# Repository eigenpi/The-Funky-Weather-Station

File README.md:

# The-Funky-Weather-Station

## Description

This is a weather-station device built with an ESP32-C3 board and a Waveshare 2.9" e-paper display. It retrieves weather info from OpenWeatherMap. Time and date is also retrieved and displayed. Device needs access to a WiFi router. This repository contains all the design files for anyone to be able to replicate it.

## Video description

https://youtu.be/MDfy2SWch-s

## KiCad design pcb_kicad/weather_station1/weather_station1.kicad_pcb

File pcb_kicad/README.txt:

This is the entire project in KiCAD 9.0.6

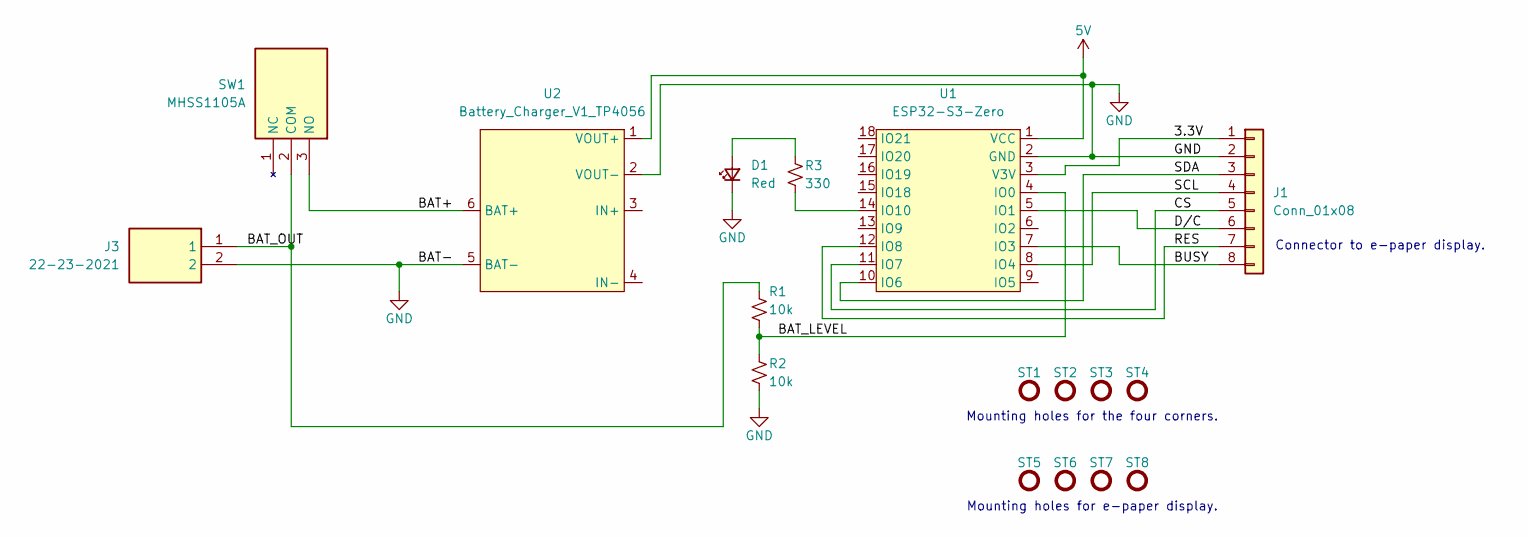
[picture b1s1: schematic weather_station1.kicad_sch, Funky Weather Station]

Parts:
D1: Red; LED_5mm_PTH_Red_NoSilk
J1: Conn_01x08; 1x08_P2.54mm
J3: 22-23-2021; SHDR2W87P0X254_1X2_493X635X1105P; Mouser Part Number 538-22-23-2021
R1, R2: 10k; R_Axial_DIN0207_L6.3mm_D2.5mm_P7.62mm_Horizontal
R3: 330; R_Axial_DIN0207_L6.3mm_D2.5mm_P7.62mm_Horizontal
ST1, ST2, ST3, ST4, ST5, ST6, ST7, ST8: Standoff; Standoff_Hole-2.75mm_Clearance-1.625mm
SW1: MHSS1105A; Mouser Part Number 642-MHSS1105A
U1: ESP32-S3-Zero; Waveshare-ESP32-C3-Zero
U2: Battery_Charger_V1_TP4056

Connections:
5V: U1.1 (VCC), U2.1 (VOUT+)
/3.3V: J1.1, U1.3 (V3V)
/BAT+: SW1.3 (NO), U2.6 (BAT+)
/BAT_LEVEL: R1.1, R2.2, U1.4 (IO0)
/BAT_OUT: J3.1, R1.2, SW1.2 (COM)
/BUSY: J1.8, U1.7 (IO3)
/CS: J1.5, U1.11 (IO7)
/D/C: J1.6, U1.5 (IO1)
/RES: J1.7, U1.12 (IO8)
/SCL: J1.4, U1.8 (IO4)
/SDA: J1.3, U1.10 (IO6)
GND: D1.1 (K), J1.2, J3.2, R2.1, U1.2 (GND), U2.2 (VOUT-), U2.5 (BAT-)
unnamed: D1.2 (A), R3.2
unnamed: R3.1, U1.14 (IO10)

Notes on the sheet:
Mounting holes for e-paper display.
Connector to e-paper display.
Mounting holes for the four corners.

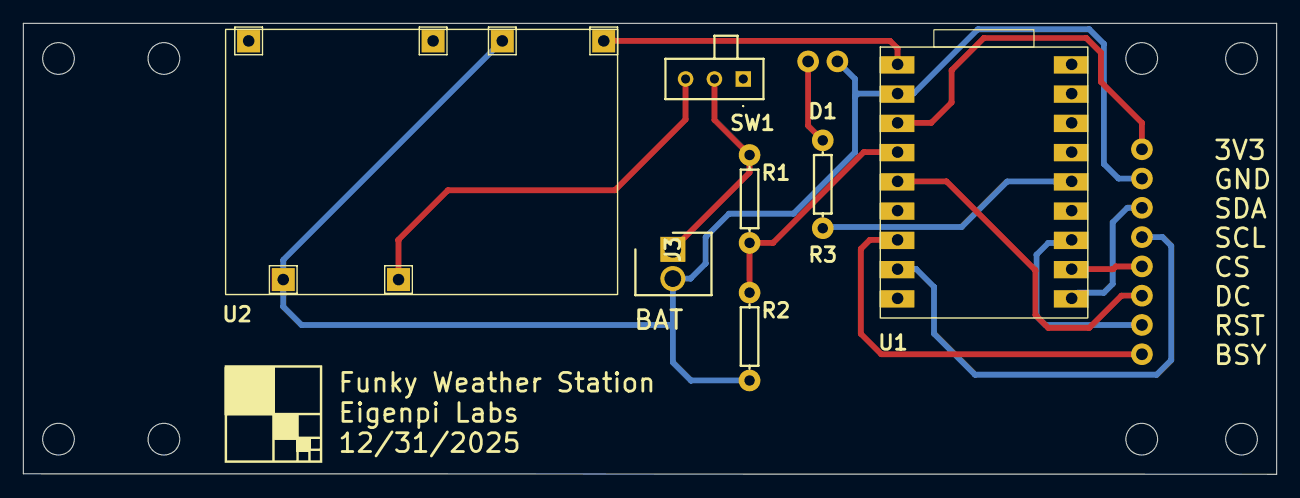
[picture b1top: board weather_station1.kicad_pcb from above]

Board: 2 copper layers, 108.7 x 39.1 mm, 17 parts (0 on the bottom side), 14 nets.
